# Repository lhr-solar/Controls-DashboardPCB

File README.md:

# Controls Leader

This board is the central hub for human machine interface inputs on the vehicle. It reads switch states, detects faults, and coordinates lighting commands across the vehicle network while maintaining robust error reporting.

## Hardware Architecture

### Power Delivery

- Main 24 V supply with ground input
- Buck regulator for MCU and Peripheral Sensing/Output Modules (PSOMs)
- Isolated power and ground dedicated to CAN interface(s)

### CAN Interfaces

- **2× CAN Transceiver Chips** with dedicated in/out connector pairs:
  - Controls CAN (lighting/peripheral network)
  - Car CAN (vehicle state network)

### Input Interfaces

#### Dashboard I/O

- Ignition switch
- Gear selector switch
- Cruise control enable/set buttons
- Regen enable button
- Hazard lights switch
- Supplemental battery switch (isolated input)

#### Steering Wheel I/O

- Left/right turn indicators
- Horn button
- Regen active indicator

## Software Functionality
TBD

## Repository Structure

```
hardware/
├── ControlsLeader_PCB/
│   ├── jkcpcb/
│   ├── lib/
│   ├── *.kicad_sch (schematic files)
│   └── *.kicad_pcb (PCB layout)
├── 3d_models/
├── Silkscreens/
└── fab/

firmware/

```

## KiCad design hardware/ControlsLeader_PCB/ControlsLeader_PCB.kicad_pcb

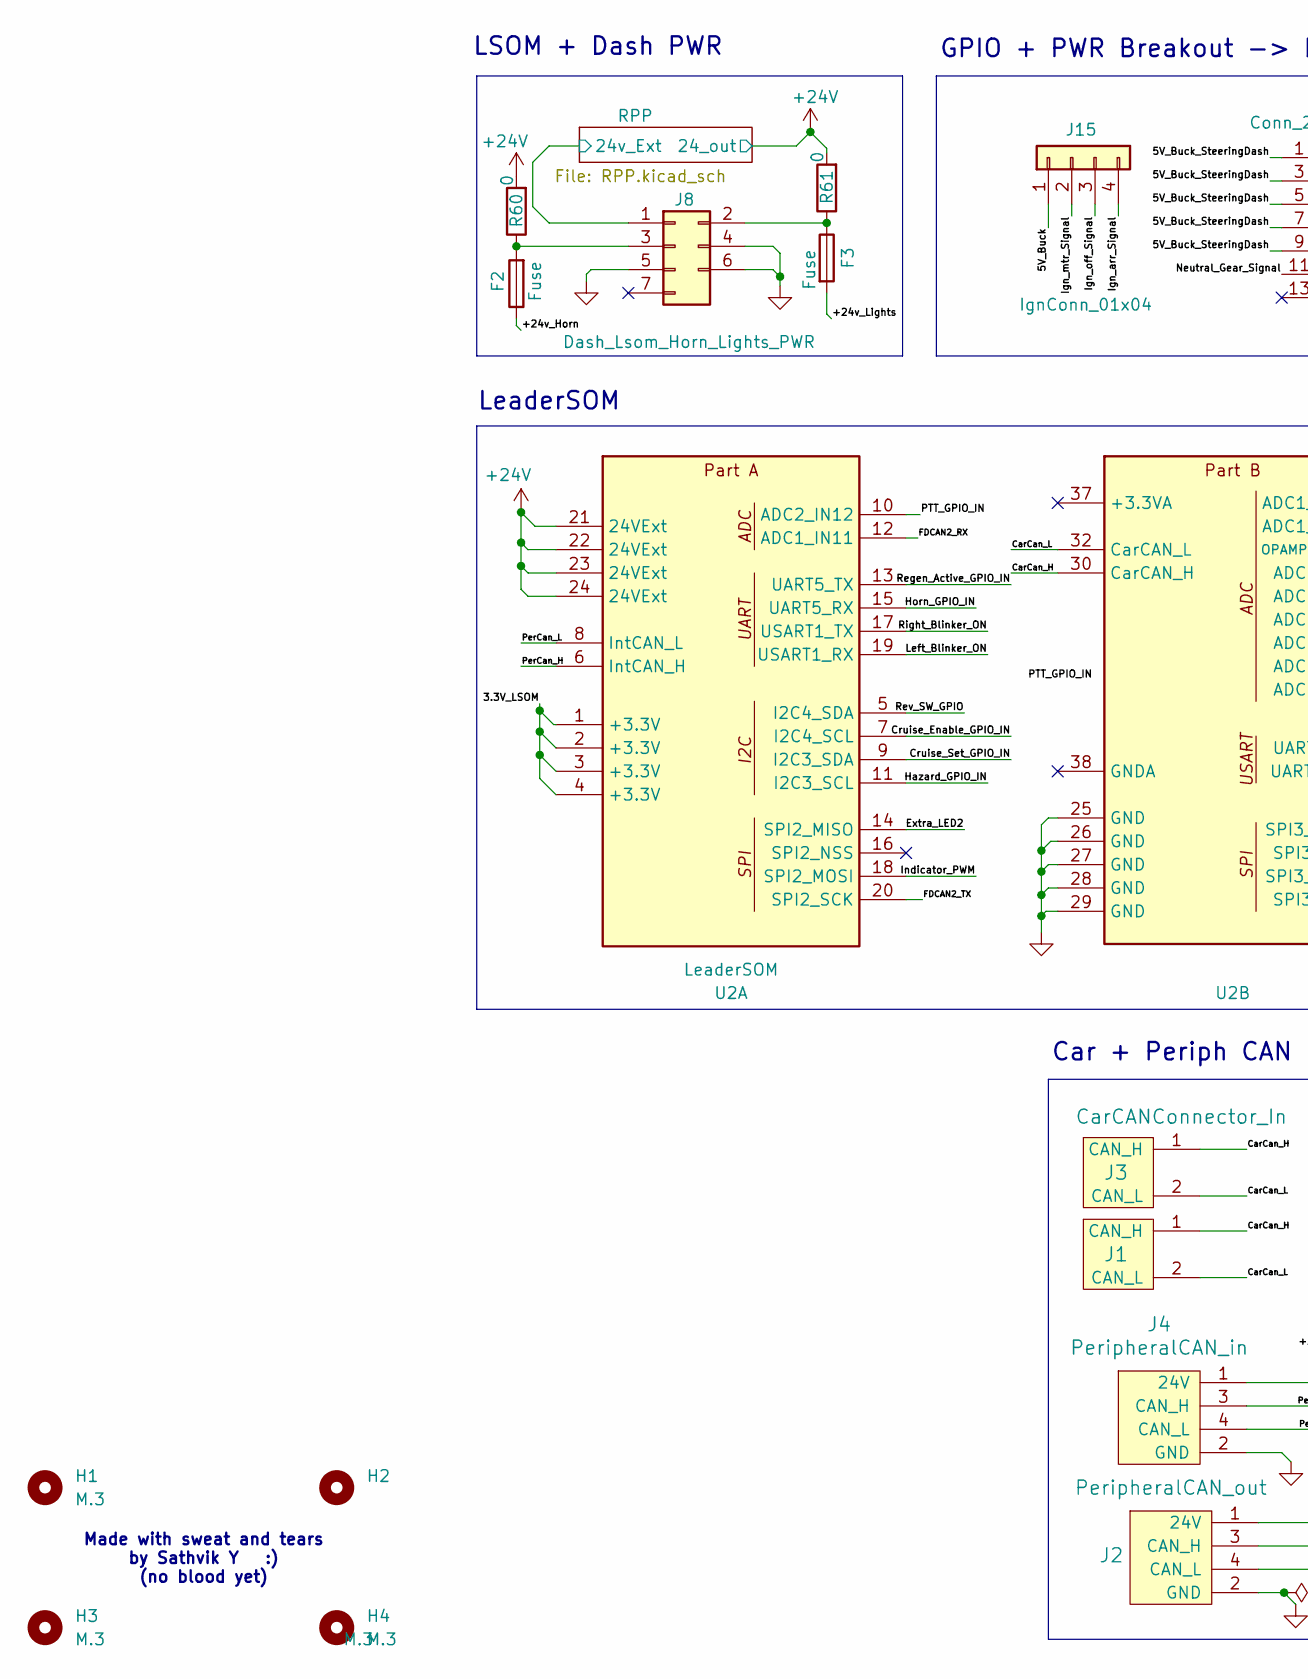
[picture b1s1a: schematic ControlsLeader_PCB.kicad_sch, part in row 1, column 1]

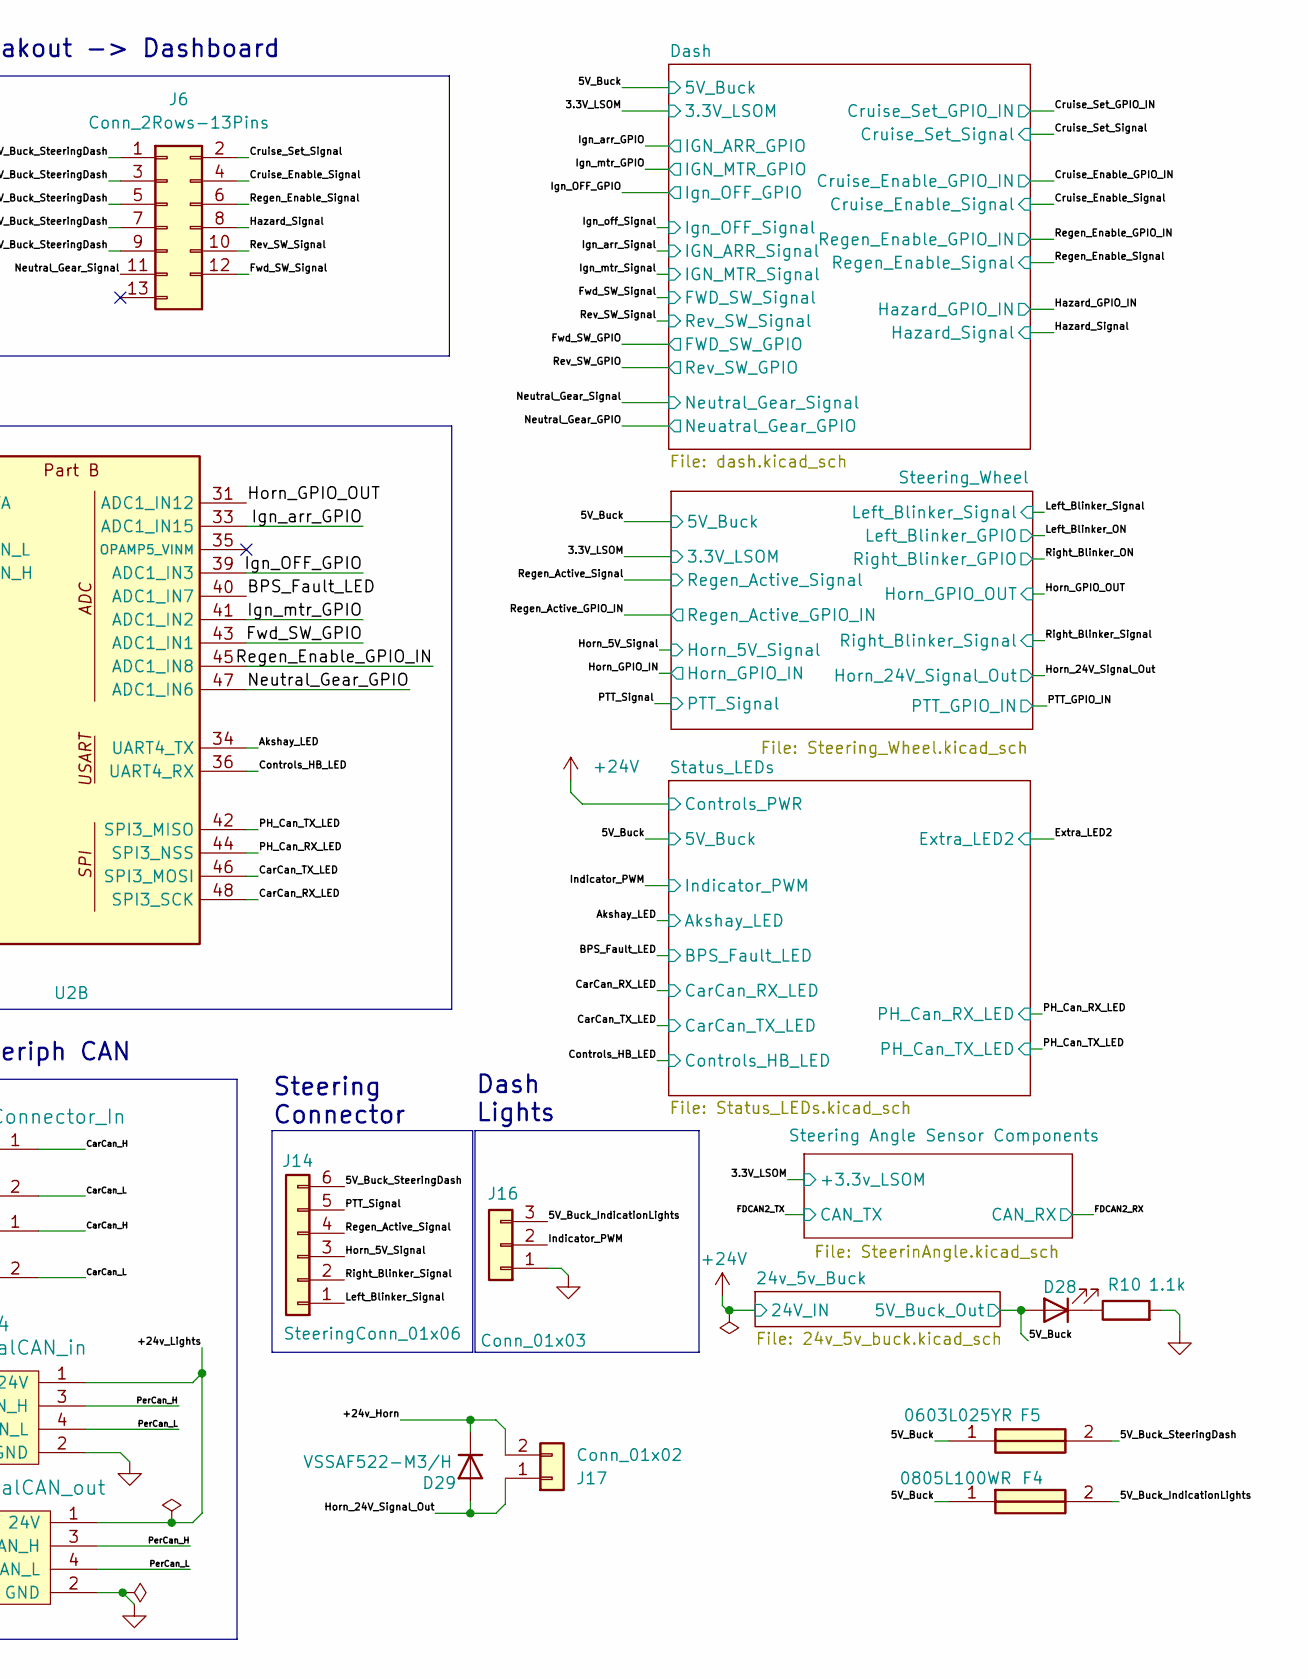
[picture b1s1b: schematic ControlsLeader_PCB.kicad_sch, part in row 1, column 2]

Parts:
D28: Controls_Leader_Status_Red; LED_0603_1608Metric_Pad1.05x0.95mm_HandSolder
D29: VSSAF522-M3/H; D_SOD-123F
F2, F3: Fuse; Fuseholder_Blade_Mini_Keystone_3568
F4: 0805L100WR; FUSC2114X180N; Mouser Part Number 576-0805L100
F5: 0603L025YR; FUSC1608X75N; Mouser Part Number 576-0603L025YR
H1, H2, H3, H4: M.3; MountingHole_3.2mm_M3_Pad_TopBottom
J1: CarCANConnector_Out; Molex_Nano-Fit_105313-xx02_1x02_P2.50mm_Horizontal
J2: PeripheralCAN_out; Molex_Nano-Fit_105313-xx04_1x04_P2.50mm_Horizontal
J3: CarCANConnector_In; Molex_Nano-Fit_105313-xx02_1x02_P2.50mm_Horizontal
J4: PeripheralCAN_in; Molex_Nano-Fit_105313-xx04_1x04_P2.50mm_Horizontal
J6: Conn_2Rows-13Pins; Molex_Nano-Fit_105314-xx12_2x06_P2.50mm_Horizontal
J8: Dash_Lsom_Horn_Lights_PWR; Molex_Nano-Fit_105314-xx06_2x03_P2.50mm_Horizontal
J14: SteeringConn_01x06; Molex_Nano-Fit_105313-xx06_1x06_P2.50mm_Horizontal
J15: IgnConn_01x04; Molex_Nano-Fit_105313-xx04_1x04_P2.50mm_Horizontal
J16: Conn_01x03; Molex_Nano-Fit_105313-xx03_1x03_P2.50mm_Horizontal
J17: Conn_01x02; Molex_Nano-Fit_105313-xx02_1x02_P2.50mm_Horizontal
R10: 1.1k; R_0603_1608Metric_Pad0.98x0.95mm_HandSolder
R60, R61: 0; R_0603_1608Metric_Pad0.98x0.95mm_HandSolder
U2: LeaderSOM

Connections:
+24V: R60.2, R61.2, U2.21 (24VExt), U2.22 (24VExt), U2.23 (24VExt), U2.24 (24VExt); also elsewhere on the board
/3.3V_LSOM: U2.1 (+3.3V), U2.2 (+3.3V), U2.3 (+3.3V), U2.4 (+3.3V); also elsewhere on the board
/5V_Buck: D28.2 (A), F4.1, F5.1, J15.1; also elsewhere on the board
/5V_Buck_IndicationLights: F4.2, J16.3
/5V_Buck_SteeringDash: F5.2, J6.1, J6.3, J6.5, J6.7, J6.9, J14.6
/+24v_Horn: D29.1 (K), F2.1, J17.2
/+24v_Lights: F3.2, J2.1 (24V), J4.1 (24V)
/Akshay_LED: U2.34 (UART4_TX); also elsewhere on the board
/BPS_Fault_LED: U2.40 (ADC1_IN7); also elsewhere on the board
/CarCan_H: J1.1 (CAN_H), J3.1 (CAN_H), U2.30 (CarCAN_H)
/CarCan_L: J1.2 (CAN_L), J3.2 (CAN_L), U2.32 (CarCAN_L)
/CarCan_RX_LED: U2.48 (SPI3_SCK); also elsewhere on the board
/CarCan_TX_LED: U2.46 (SPI3_MOSI); also elsewhere on the board
/Controls_HB_LED: U2.36 (UART4_RX); also elsewhere on the board
/Cruise_Enable_GPIO_IN: U2.7 (I2C4_SCL); also elsewhere on the board
/Cruise_Enable_Signal: J6.4; also elsewhere on the board
/Cruise_Set_GPIO_IN: U2.9 (I2C3_SDA); also elsewhere on the board
/Cruise_Set_Signal: J6.2; also elsewhere on the board
/Extra_LED2: U2.14 (SPI2_MISO); also elsewhere on the board
/FDCAN2_RX: U2.12 (ADC1_IN11); also elsewhere on the board
/FDCAN2_TX: U2.20 (SPI2_SCK); also elsewhere on the board
/Fwd_SW_GPIO: U2.43 (ADC1_IN1); also elsewhere on the board
/Fwd_SW_Signal: J6.12; also elsewhere on the board
/Hazard_GPIO_IN: U2.11 (I2C3_SCL); also elsewhere on the board
/Hazard_Signal: J6.8; also elsewhere on the board
/Horn_5V_Signal: J14.3; also elsewhere on the board
/Horn_24V_Signal_Out: D29.2 (A), J17.1; also elsewhere on the board
/Horn_GPIO_IN: U2.15 (UART5_RX); also elsewhere on the board
/Horn_GPIO_OUT: U2.31 (ADC1_IN12); also elsewhere on the board
/Ign_OFF_GPIO: U2.39 (ADC1_IN3); also elsewhere on the board
/Ign_arr_GPIO: U2.33 (ADC1_IN15); also elsewhere on the board
/Ign_arr_Signal: J15.4; also elsewhere on the board
/Ign_mtr_GPIO: U2.41 (ADC1_IN2); also elsewhere on the board
/Ign_mtr_Signal: J15.2; also elsewhere on the board
/Ign_off_Signal: J15.3; also elsewhere on the board
/Indicator_PWM: J16.2, U2.18 (SPI2_MOSI)
/Left_Blinker_ON: U2.19 (USART1_RX); also elsewhere on the board
/Left_Blinker_Signal: J14.1; also elsewhere on the board
/Neutral_Gear_GPIO: U2.47 (ADC1_IN6); also elsewhere on the board
/Neutral_Gear_Signal: J6.11; also elsewhere on the board
/PH_Can_RX_LED: U2.44 (SPI3_NSS); also elsewhere on the board
/PH_Can_TX_LED: U2.42 (SPI3_MISO); also elsewhere on the board
/PTT_GPIO_IN: U2.10 (ADC2_IN12); also elsewhere on the board
/PTT_Signal: J14.5; also elsewhere on the board
/PerCan_H: J2.3 (CAN_H), J4.3 (CAN_H), U2.6 (IntCAN_H)
/PerCan_L: J2.4 (CAN_L), J4.4 (CAN_L), U2.8 (IntCAN_L)
/RPP/LV+: J8.1; also elsewhere on the board
/Regen_Active_GPIO_IN: U2.13 (UART5_TX); also elsewhere on the board
/Regen_Active_Signal: J14.4; also elsewhere on the board
/Regen_Enable_GPIO_IN: U2.45 (ADC1_IN8); also elsewhere on the board
/Regen_Enable_Signal: J6.6; also elsewhere on the board
/Rev_SW_GPIO: U2.5 (I2C4_SDA); also elsewhere on the board
/Rev_SW_Signal: J6.10; also elsewhere on the board
/Right_Blinker_ON: U2.17 (USART1_TX); also elsewhere on the board
/Right_Blinker_Signal: J14.2; also elsewhere on the board
GND: J2.2 (GND), J4.2 (GND), J8.4, J8.5, J8.6, J16.1, R10.2, U2.25 (GND), U2.26 (GND), U2.27 (GND), U2.28 (GND), U2.29 (GND); also elsewhere on the board
unnamed: D28.1 (K), R10.1
unnamed: F3.1, J8.2, R61.1
unnamed: F2.2, J8.3, R60.1

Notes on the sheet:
Car + Periph CAN
Dash Lights
GPIO + PWR Breakout -> Dashboard
Steering Connector
LSOM + Dash PWR
LeaderSOM
Made with sweat and tears by Sathvik Y :) (no blood yet)

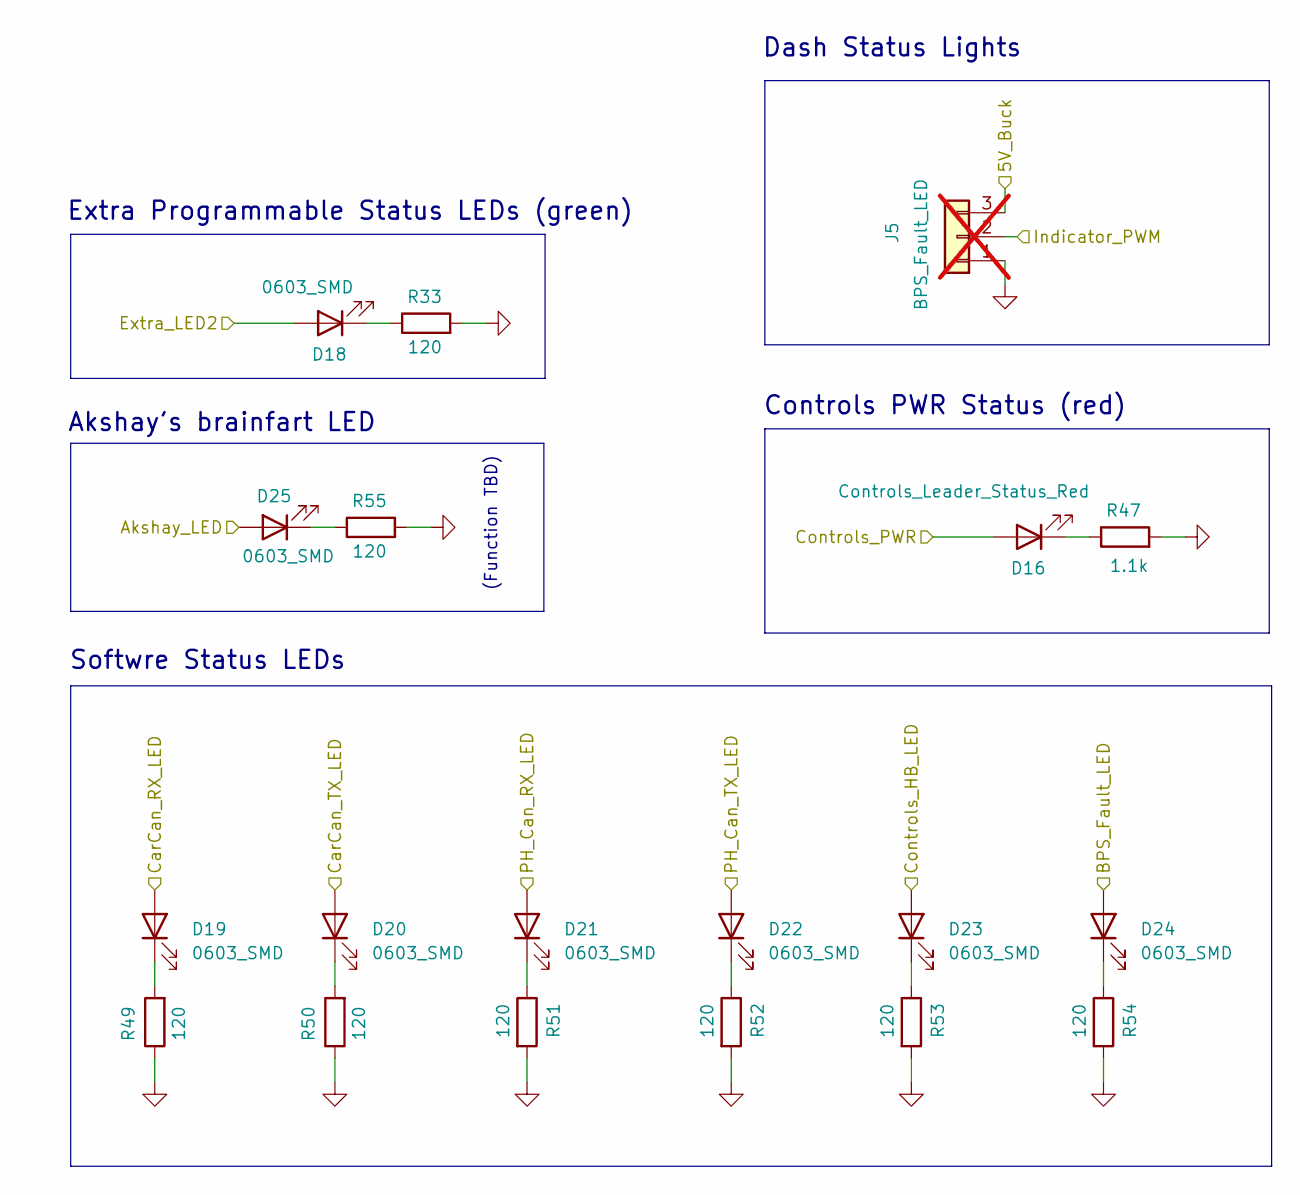
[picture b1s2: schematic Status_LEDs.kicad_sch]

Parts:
D16: Controls_Leader_Status_Red; LED_0603_1608Metric_Pad1.05x0.95mm_HandSolder
D18, D19, D20, D21, D22, D23, D24, D25: 0603_SMD; LED_0603_1608Metric_Pad1.05x0.95mm_HandSolder
J5: BPS_Fault_LED; Molex_Micro-Fit_3.0_43650-0300_1x03_P3.00mm_Horizontal; not fitted
R33, R49, R50, R51, R52, R53, R54, R55: 120; R_0603_1608Metric_Pad0.98x0.95mm_HandSolder
R47: 1.1k; R_0603_1608Metric_Pad0.98x0.95mm_HandSolder

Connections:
+24V: D16.2 (A); also elsewhere on the board
/Akshay_LED: D25.2 (A); also elsewhere on the board
/BPS_Fault_LED: D24.2 (A); also elsewhere on the board
/CarCan_RX_LED: D19.2 (A); also elsewhere on the board
/CarCan_TX_LED: D20.2 (A); also elsewhere on the board
/Controls_HB_LED: D23.2 (A); also elsewhere on the board
/Extra_LED2: D18.2 (A); also elsewhere on the board
/PH_Can_RX_LED: D21.2 (A); also elsewhere on the board
/PH_Can_TX_LED: D22.2 (A); also elsewhere on the board
GND: J5.1, R33.2, R47.2, R49.1, R50.1, R51.2, R52.2, R53.2, R54.2, R55.2; also elsewhere on the board
unnamed: D16.1 (K), R47.1
unnamed: D18.1 (K), R33.1
unnamed: D19.1 (K), R49.2
unnamed: D20.1 (K), R50.2
unnamed: D21.1 (K), R51.1
unnamed: D22.1 (K), R52.1
unnamed: D23.1 (K), R53.1
unnamed: D24.1 (K), R54.1
unnamed: D25.1 (K), R55.1

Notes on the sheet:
Akshay's brainfart LED
Extra Programmable Status LEDs (green)
Softwre Status LEDs
Controls PWR Status (red)
(Function TBD)
Dash Status Lights

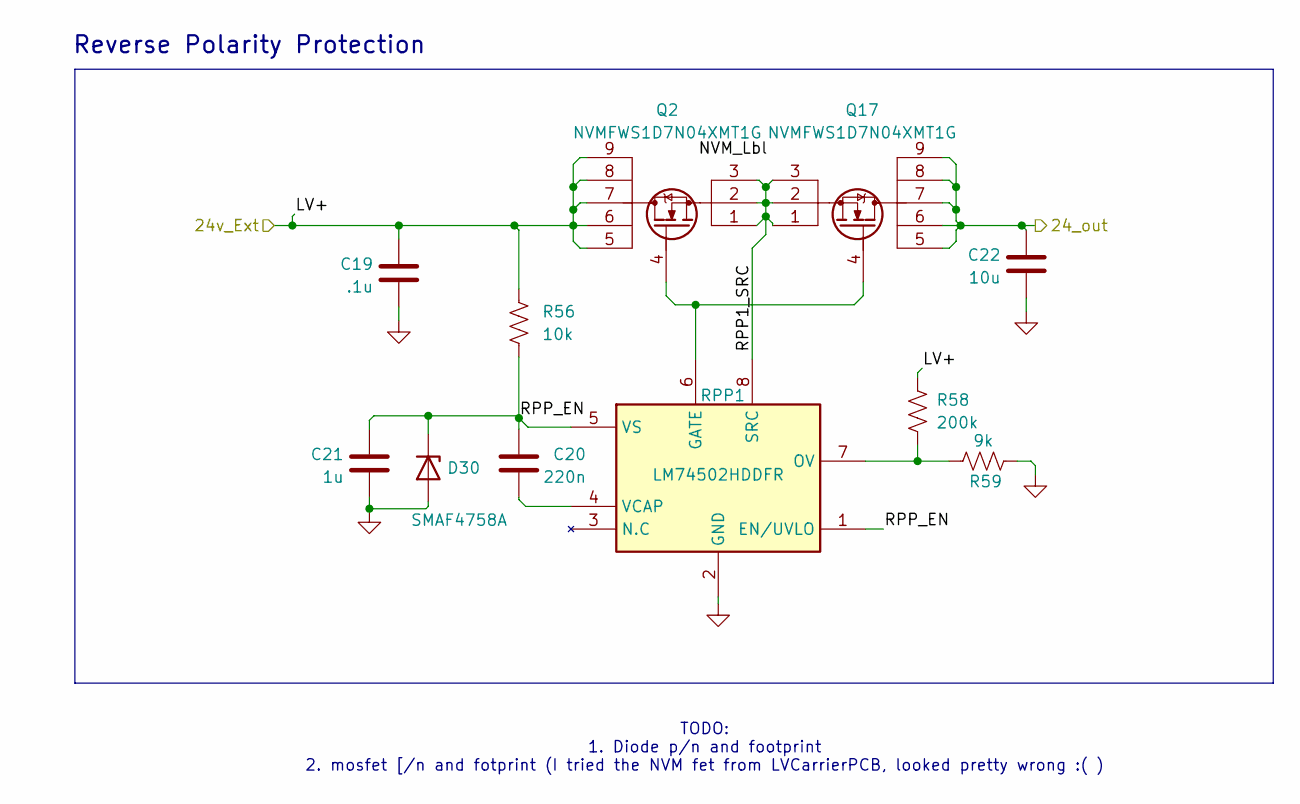
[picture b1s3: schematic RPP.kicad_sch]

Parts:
C19: .1u; C_0603_1608Metric_Pad1.08x0.95mm_HandSolder; Manufacturer_Part_Number 06035C223K4T4A
C20: 220n; C_0603_1608Metric_Pad1.08x0.95mm_HandSolder; Manufacturer_Part_Number 06035C223K4T4A
C21: 1u; C_0603_1608Metric_Pad1.08x0.95mm_HandSolder; Manufacturer_Part_Number 06035C223K4T4A
C22: 10u; C_0603_1608Metric_Pad1.08x0.95mm_HandSolder; Manufacturer_Part_Number 06035C223K4T4A
D30: SMAF4758A; SODFL5026X125N
Q2, Q17: NVMFWS1D7N04XMT1G; NVMFWS3D0P04M8LT1G
R56: 10k; R_0603_1608Metric_Pad0.98x0.95mm_HandSolder; Manufacturer_Part_Number CRCW060310K0FKEI
R58: 200k; R_0603_1608Metric_Pad0.98x0.95mm_HandSolder; Manufacturer_Part_Number CRCW060310K0FKEI
R59: 9k; R_0603_1608Metric_Pad0.98x0.95mm_HandSolder; Manufacturer_Part_Number CRCW060310K0FKEI
RPP1: LM74502HDDFR; SOT65P280X110-8N; Mouser Part Number 595-LM74502HDDFR

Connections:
+24V: C22.2, Q17.5, Q17.6, Q17.7, Q17.8, Q17.9; also elsewhere on the board
/RPP/LV+: C19.2, Q2.5, Q2.6, Q2.7, Q2.8, Q2.9, R56.1, R58.1; also elsewhere on the board
/RPP/RPP1_SRC: Q2.1, Q2.2, Q2.3, Q17.1, Q17.2, Q17.3, RPP1.8 (SRC)
/RPP/RPP_EN: C20.2, C21.2, D30.1 (K), R56.2, RPP1.1 (EN/UVLO), RPP1.5 (VS)
GND: C19.1, C21.1, C22.1, D30.2 (A), R59.2, RPP1.2 (GND); also elsewhere on the board
unnamed: Q2.4, Q17.4, RPP1.6 (GATE)
unnamed: R58.2, R59.1, RPP1.7 (OV)
unnamed: C20.1, RPP1.4 (VCAP)

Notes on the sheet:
TODO: 1. Diode p/n and footprint 2. mosfet [/n and fotprint (I tried the NVM fet from LVCarrierPCB, looked pretty wrong :( )
Reverse Polarity Protection

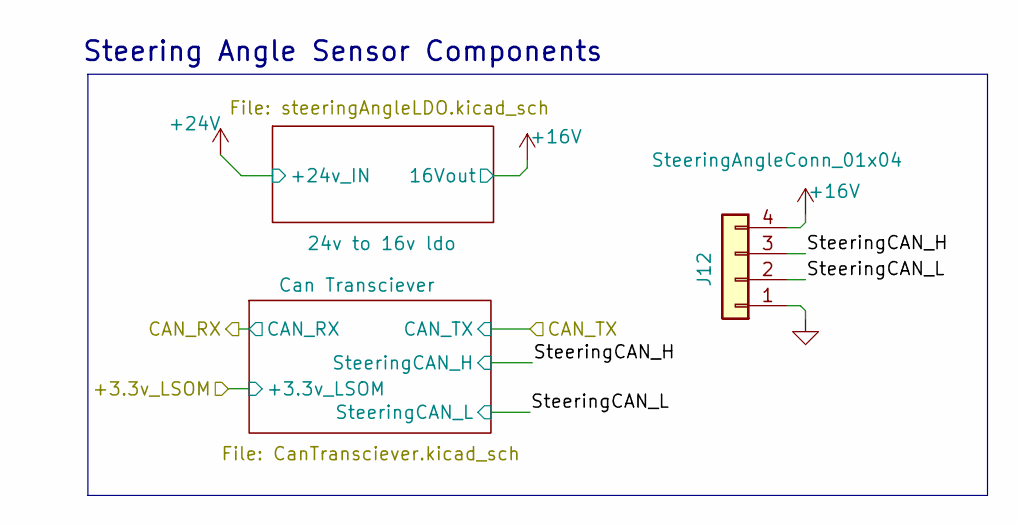
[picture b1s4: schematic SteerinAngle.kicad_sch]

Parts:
J12: SteeringAngleConn_01x04; Molex_Nano-Fit_105313-xx04_1x04_P2.50mm_Horizontal

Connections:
+16V: J12.4; also elsewhere on the board
/Steering Angle Sensor Components/SteeringCAN_H: J12.3; also elsewhere on the board
/Steering Angle Sensor Components/SteeringCAN_L: J12.2; also elsewhere on the board
GND: J12.1; also elsewhere on the board

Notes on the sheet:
Steering Angle Sensor Components

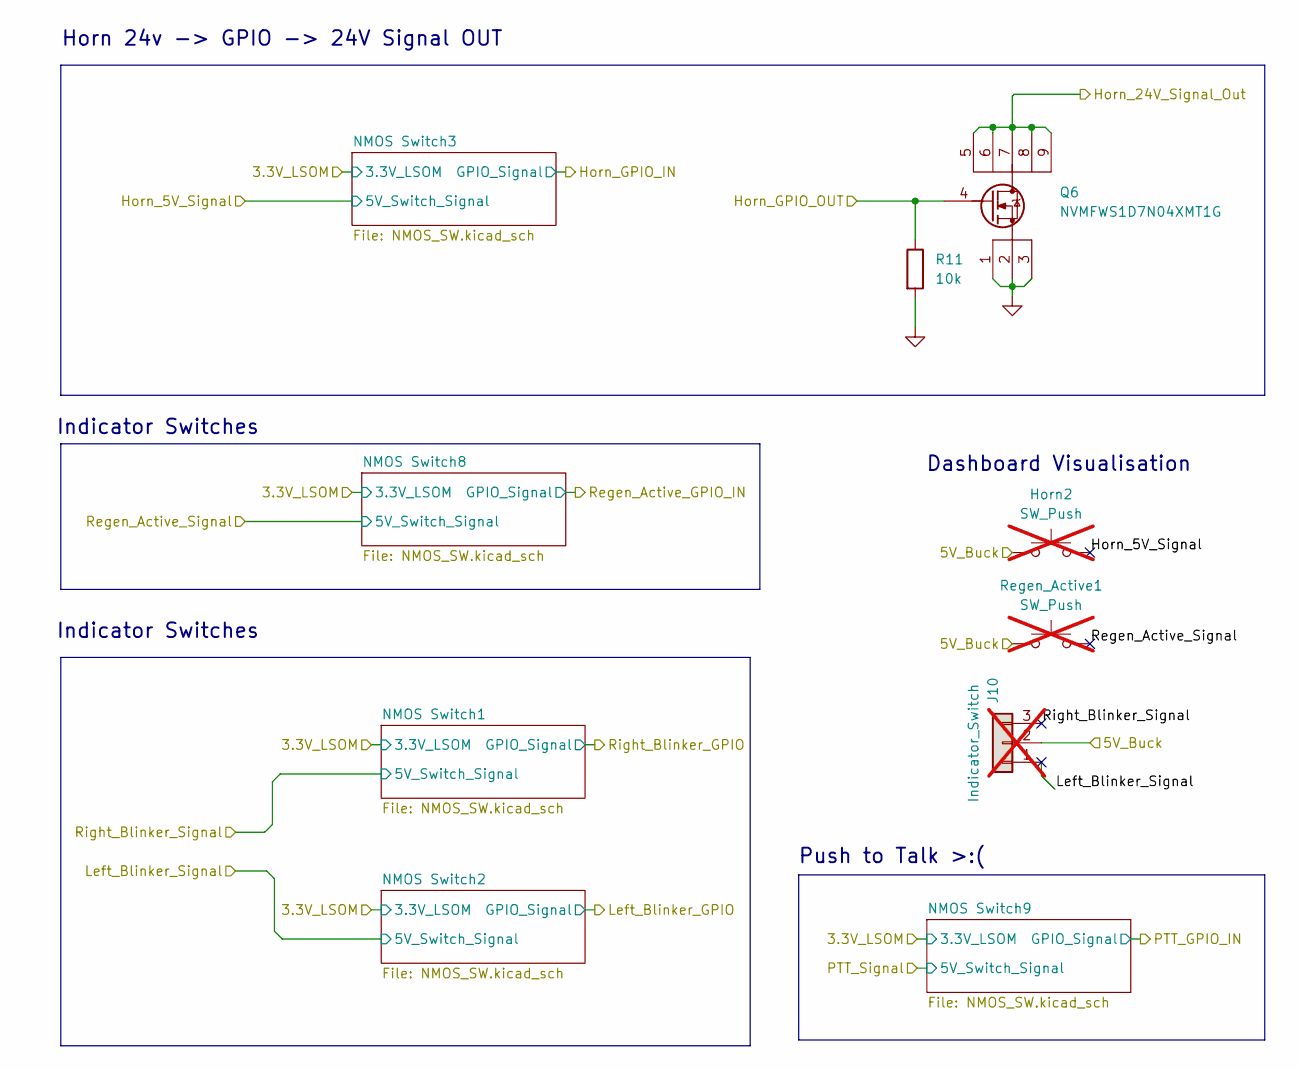
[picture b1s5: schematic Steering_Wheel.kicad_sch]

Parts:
Horn2: SW_Push; Molex_Nano-Fit_105313-xx02_1x02_P2.50mm_Horizontal; not fitted
J10: Indicator_Switch; Molex_Nano-Fit_105313-xx03_1x03_P2.50mm_Horizontal; not fitted
Q6: NVMFWS1D7N04XMT1G; NVMFWS3D0P04M8LT1G
R11: 10k; R_0603_1608Metric_Pad0.98x0.95mm_HandSolder
Regen_Active1: SW_Push; Molex_Nano-Fit_105313-xx02_1x02_P2.50mm_Horizontal; not fitted

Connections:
/Horn_24V_Signal_Out: Q6.5, Q6.6, Q6.7, Q6.8, Q6.9; also elsewhere on the board
/Horn_GPIO_OUT: Q6.4, R11.1; also elsewhere on the board
GND: Q6.1, Q6.2, Q6.3, R11.2; also elsewhere on the board
unnamed: Horn2.1, J10.2, Regen_Active1.1

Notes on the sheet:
Push to Talk >:(
Indicator Switches
Horn 24v -> GPIO -> 24V Signal OUT
Dashboard Visualisation

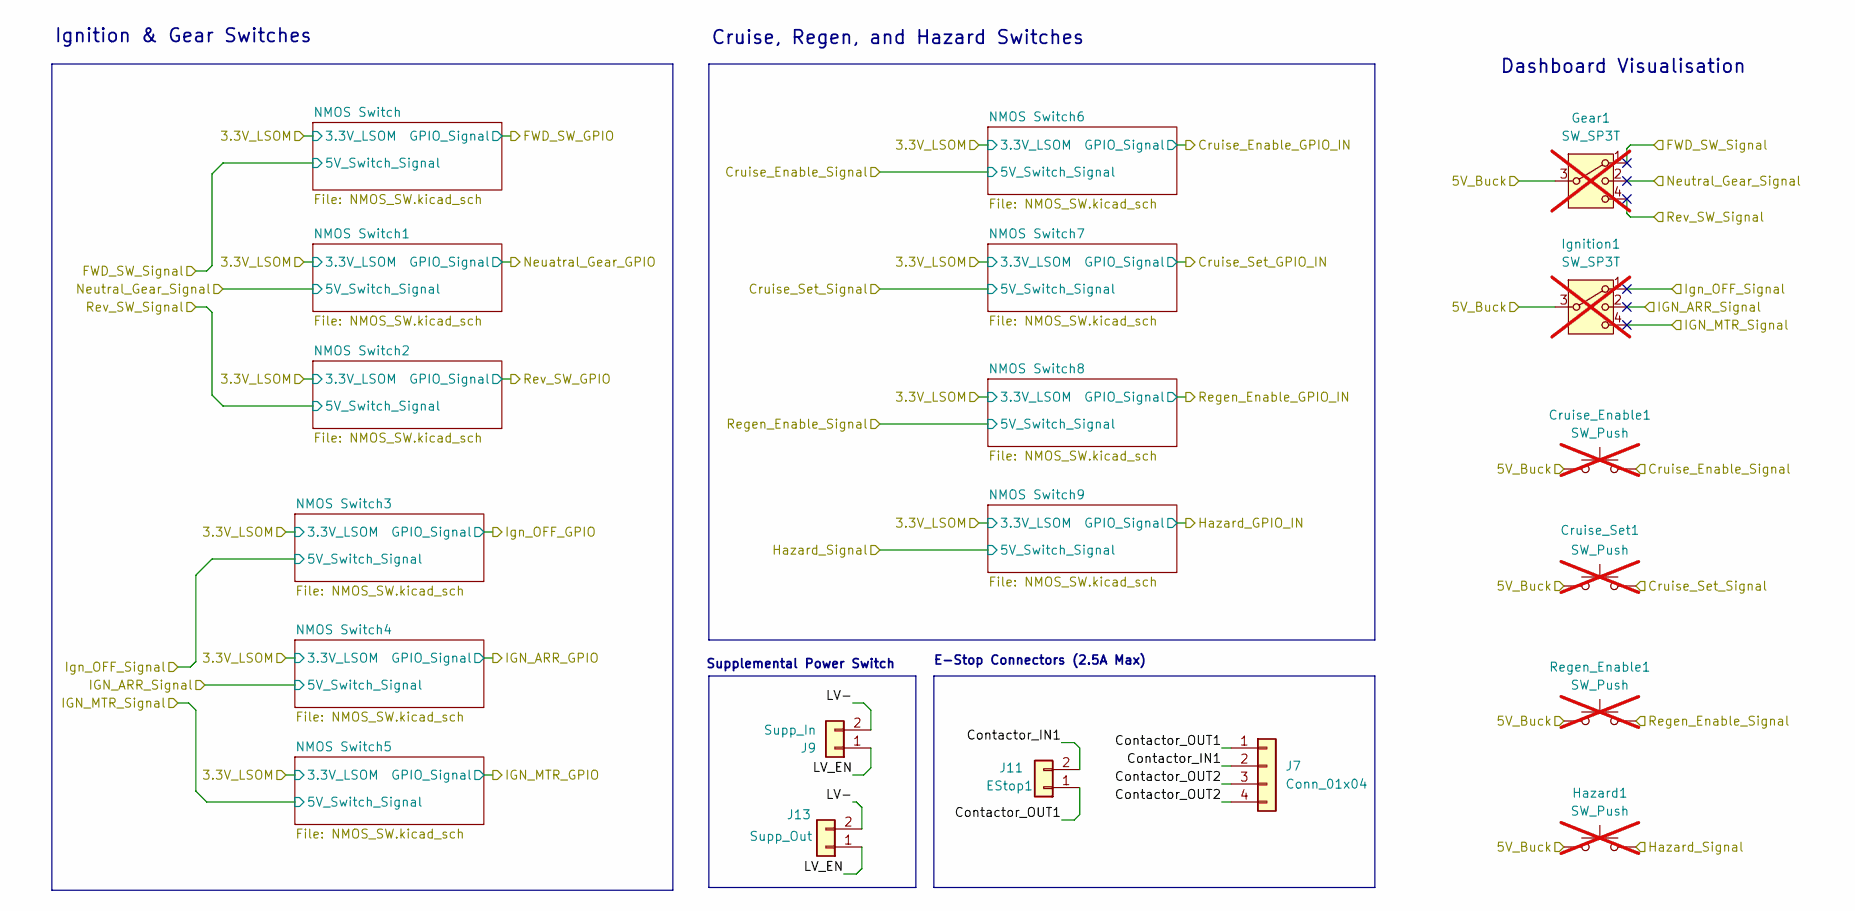
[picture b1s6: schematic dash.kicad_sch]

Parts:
Cruise_Enable1: SW_Push; Molex_Nano-Fit_105313-xx02_1x02_P2.50mm_Horizontal; not fitted
Cruise_Set1: SW_Push; Molex_Nano-Fit_105313-xx02_1x02_P2.50mm_Horizontal; not fitted
Gear1: SW_SP3T; CONN_SD-105313-100_04_MOL; not fitted
Hazard1: SW_Push; Molex_Nano-Fit_105313-xx02_1x02_P2.50mm_Horizontal; not fitted
Ignition1: SW_SP3T; CONN_SD-105313-100_04_MOL; not fitted
J7: Conn_01x04; Molex_Nano-Fit_105313-xx04_1x04_P2.50mm_Horizontal
J9: Supp_In; Molex_Nano-Fit_105313-xx02_1x02_P2.50mm_Horizontal
J11: EStop1; Molex_Nano-Fit_105313-xx02_1x02_P2.50mm_Horizontal
J13: Supp_Out; Molex_Nano-Fit_105313-xx02_1x02_P2.50mm_Horizontal
Regen_Enable1: SW_Push; Molex_Nano-Fit_105313-xx02_1x02_P2.50mm_Horizontal; not fitted

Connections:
/Dash/Contactor_IN1: J7.2, J11.2
/Dash/Contactor_OUT1: J7.1, J11.1
/Dash/Contactor_OUT2: J7.3, J7.4
/Dash/LV-: J9.2, J13.2
/Dash/LV_EN: J9.1, J13.1
unnamed: Cruise_Enable1.1, Cruise_Set1.1, Gear1.3, Hazard1.1, Ignition1.3, Regen_Enable1.1

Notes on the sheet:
E-Stop Connectors (2.5A Max)
Dashboard Visualisation
Cruise, Regen, and Hazard Switches
Ignition & Gear Switches
Supplemental Power Switch

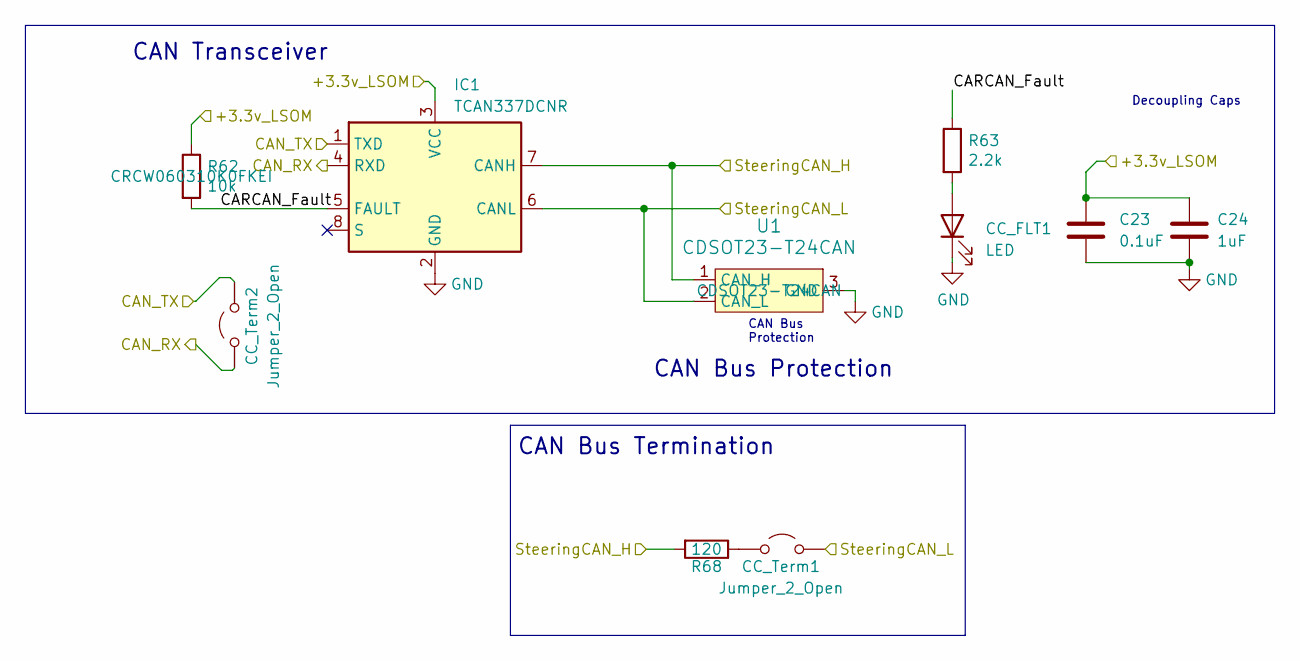
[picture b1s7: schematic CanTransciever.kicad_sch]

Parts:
C23: 0.1uF; C_0603_1608Metric_Pad1.08x0.95mm_HandSolder; Mouser Part Number MLASH168SB7104KTNA01
C24: 1uF; C_0603_1608Metric_Pad1.08x0.95mm_HandSolder; Mouser Part Number MLASU168SB5105KTNA01
CC_FLT1: LED; LED_0603_1608Metric_Pad1.05x0.95mm_HandSolder; Mouser Part Number 604-APTD2012LCGCK
CC_Term1, CC_Term2: Jumper_2_Open; PinHeader_1x02_P2.54mm_Vertical
IC1: TCAN337DCNR; Mouser Part Number 595-TCAN337DCNR
R62: 10k; R_0603_1608Metric_Pad0.98x0.95mm_HandSolder; Mouser Part Number CRCW060310K0FKEI
R63: 2.2k; R_0603_1608Metric_Pad0.98x0.95mm_HandSolder; Mouser Part Number CRCW06032K10FKEA
R68: 120; R_0603_1608Metric_Pad0.98x0.95mm_HandSolder; Mouser Part Number CRCW0603120RFKEC
U1: CDSOT23-T24CAN; Mouser Part Number CDSOT23-T24CAN

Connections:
/3.3V_LSOM: C23.1, C24.1, IC1.3 (VCC), R62.1; also elsewhere on the board
/FDCAN2_RX: CC_Term2.1 (A), IC1.4 (RXD); also elsewhere on the board
/FDCAN2_TX: CC_Term2.2 (B), IC1.1 (TXD); also elsewhere on the board
/Steering Angle Sensor Components/Can Transciever/CARCAN_Fault: IC1.5 (FAULT), R62.2, R63.1
/Steering Angle Sensor Components/SteeringCAN_H: IC1.7 (CANH), R68.2, U1.1 (CAN_H); also elsewhere on the board
/Steering Angle Sensor Components/SteeringCAN_L: CC_Term1.2 (B), IC1.6 (CANL), U1.2 (CAN_L); also elsewhere on the board
GND: C23.2, C24.2, CC_FLT1.1 (K), IC1.2 (GND), U1.3 (GND); also elsewhere on the board
unnamed: CC_FLT1.2 (A), R63.2
unnamed: CC_Term1.1 (A), R68.1

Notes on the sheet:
CAN Bus Protection
Decoupling Caps
CAN Bus Protection
CAN Transceiver
CAN Bus Termination

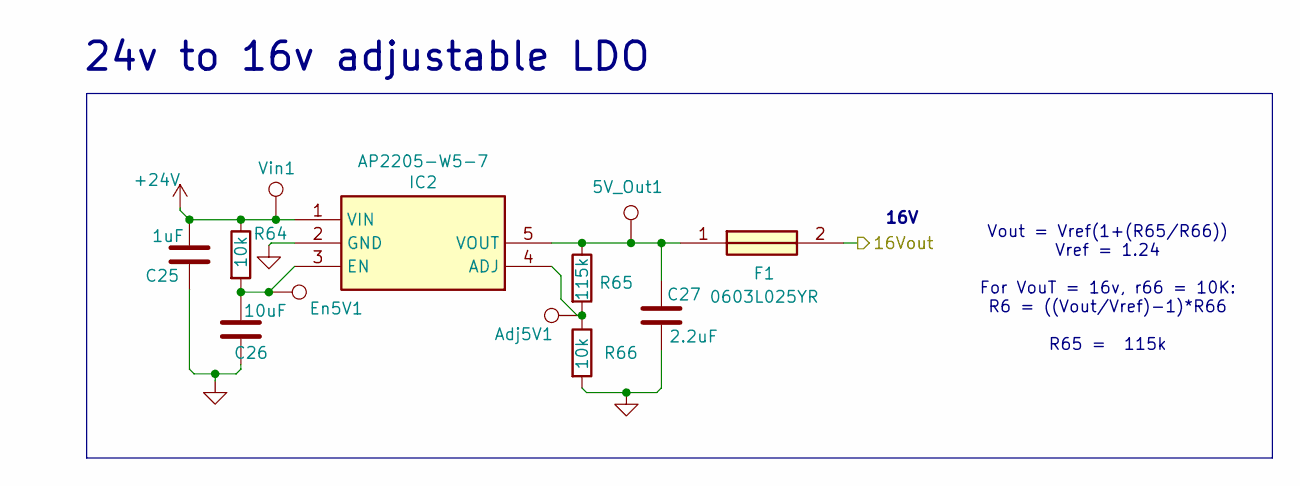
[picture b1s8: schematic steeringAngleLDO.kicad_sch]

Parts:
5V_Out1: 5V_Out; TestPoint_Pad_1.0x1.0mm
Adj5V1: Adj5V; TestPoint_Pad_1.0x1.0mm
C25: 1uF; C_0603_1608Metric_Pad1.08x0.95mm_HandSolder
C26: 10uF; C_0603_1608Metric_Pad1.08x0.95mm_HandSolder
C27: 2.2uF; C_0603_1608Metric_Pad1.08x0.95mm_HandSolder
En5V1: Enable5V; TestPoint_Pad_1.0x1.0mm
F1: 0603L025YR; FUSC1608X75N; Mouser Part Number 576-0603L025YR
IC2: AP2205-W5-7; AP2205W57; Mouser Part Number 621-AP2205-W5-7
R64, R66: 10k; R_0603_1608Metric_Pad0.98x0.95mm_HandSolder
R65: 115k; R_0603_1608Metric_Pad0.98x0.95mm_HandSolder
Vin1: Vin; TestPoint_Pad_1.0x1.0mm

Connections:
+16V: F1.2; also elsewhere on the board
+24V: C25.2, IC2.1 (VIN), R64.1, Vin1.1; also elsewhere on the board
/Steering Angle Sensor Components/24v to 16v ldo/16v_prefuse: 5V_Out1.1, C27.1, F1.1, IC2.5 (VOUT), R65.1; also elsewhere on the board
GND: C25.1, C26.1, C27.2, IC2.2 (GND), R66.2; also elsewhere on the board
unnamed 100: Adj5V1.1, IC2.4 (ADJ), R65.2, R66.1; also elsewhere on the board
unnamed 101: C26.2, En5V1.1, IC2.3 (EN), R64.2; also elsewhere on the board

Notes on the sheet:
Vout = Vref(1+(R65/R66)) Vref = 1.24 For VouT = 16v, r66 = 10K: R6 = ((Vout/Vref)-1)*R66 R65 = 115k
24v to 16v adjustable LDO
16V

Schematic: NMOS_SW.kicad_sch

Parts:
C1: 2.2uF; C_0603_1608Metric_Pad1.08x0.95mm_HandSolder
D1: GPIO_Status_Blue; LED_0603_1608Metric_Pad1.05x0.95mm_HandSolder
Q1: NMOS; SOT23
R1: 10k; R_0603_1608Metric_Pad0.98x0.95mm_HandSolder
R9: 150; R_0603_1608Metric_Pad0.98x0.95mm_HandSolder
R31: 100k; R_0603_1608Metric_Pad0.98x0.95mm_HandSolder
TP1: TestPoint; TestPoint_Pad_1.0x1.0mm

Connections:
/3.3V_LSOM: R31.1; also elsewhere on the board
/Regen_Active_GPIO_IN: Q1.1 (D), R31.2, TP1.1; also elsewhere on the board
/Regen_Active_Signal: C1.2, D1.2 (A), Q1.2 (G), R1.2; also elsewhere on the board
GND: C1.1, Q1.3 (S), R1.1, R9.2; also elsewhere on the board
unnamed: D1.1 (K), R9.1

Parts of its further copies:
C2, C3, C4, C5, C6, C7, C8, C9, C10, C11, C12, C13, C14, C28: 2.2uF; C_0603_1608Metric_Pad1.08x0.95mm_HandSolder
D2, D3, D5, D6, D7, D8, D9, D10, D11, D12, D13, D14, D15, D17: GPIO_Status_Blue; LED_0603_1608Metric_Pad1.05x0.95mm_HandSolder
Q3, Q4, Q5, Q7, Q8, Q9, Q10, Q11, Q12, Q13, Q14, Q15, Q16, Q18: NMOS; SOT23
R2, R3, R4, R5, R6, R7, R8, R12, R13, R14, R15, R16, R17, R45: 10k; R_0603_1608Metric_Pad0.98x0.95mm_HandSolder
R18, R19, R20, R21, R22, R23, R24, R25, R26, R27, R28, R29, R30, R46: 150; R_0603_1608Metric_Pad0.98x0.95mm_HandSolder
R32, R34, R35, R36, R37, R38, R39, R40, R41, R42, R43, R44, R57, R67: 100k; R_0603_1608Metric_Pad0.98x0.95mm_HandSolder
TP2, TP3, TP4, TP5, TP6, TP7, TP8, TP9, TP10, TP11, TP12, TP13, TP14, TP15: TestPoint; TestPoint_Pad_1.0x1.0mm

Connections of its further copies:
/3.3V_LSOM: R32.1, R34.1, R35.1, R36.1, R37.1, R38.1, R39.1, R40.1, R41.1, R42.1, R43.1, R44.1, R57.1, R67.1; also elsewhere on the board
/Cruise_Enable_GPIO_IN: Q10.1 (D), R39.2, TP8.1; also elsewhere on the board
/Cruise_Enable_Signal: C8.2, D9.2 (A), Q10.2 (G), R8.2; also elsewhere on the board
/Cruise_Set_GPIO_IN: Q11.1 (D), R40.2, TP9.1; also elsewhere on the board
/Cruise_Set_Signal: C9.2, D10.2 (A), Q11.2 (G), R12.2; also elsewhere on the board
/Fwd_SW_GPIO: Q3.1 (D), R32.2, TP2.1; also elsewhere on the board
/Fwd_SW_Signal: C2.2, D2.2 (A), Q3.2 (G), R2.2; also elsewhere on the board
/Hazard_GPIO_IN: Q13.1 (D), R42.2, TP11.1; also elsewhere on the board
/Hazard_Signal: C11.2, D12.2 (A), Q13.2 (G), R14.2; also elsewhere on the board
/Horn_5V_Signal: C12.2, D13.2 (A), Q14.2 (G), R15.2; also elsewhere on the board
/Horn_GPIO_IN: Q14.1 (D), R43.2, TP12.1; also elsewhere on the board
/Ign_OFF_GPIO: Q7.1 (D), R36.2, TP5.1; also elsewhere on the board
/Ign_arr_GPIO: Q8.1 (D), R37.2, TP6.1; also elsewhere on the board
/Ign_arr_Signal: C6.2, D7.2 (A), Q8.2 (G), R6.2; also elsewhere on the board
/Ign_mtr_GPIO: Q9.1 (D), R38.2, TP7.1; also elsewhere on the board
/Ign_mtr_Signal: C7.2, D8.2 (A), Q9.2 (G), R7.2; also elsewhere on the board
/Ign_off_Signal: C5.2, D6.2 (A), Q7.2 (G), R5.2; also elsewhere on the board
/Left_Blinker_ON: Q16.1 (D), R57.2, TP15.1; also elsewhere on the board
/Left_Blinker_Signal: C14.2, D15.2 (A), Q16.2 (G), R17.2; also elsewhere on the board
/Neutral_Gear_GPIO: Q4.1 (D), R34.2, TP3.1; also elsewhere on the board
/Neutral_Gear_Signal: C3.2, D3.2 (A), Q4.2 (G), R3.2; also elsewhere on the board
/PTT_GPIO_IN: Q18.1 (D), R67.2, TP14.1; also elsewhere on the board
/PTT_Signal: C28.2, D17.2 (A), Q18.2 (G), R45.2; also elsewhere on the board
/Regen_Enable_GPIO_IN: Q12.1 (D), R41.2, TP10.1; also elsewhere on the board
/Regen_Enable_Signal: C10.2, D11.2 (A), Q12.2 (G), R13.2; also elsewhere on the board
/Rev_SW_GPIO: Q5.1 (D), R35.2, TP4.1; also elsewhere on the board
/Rev_SW_Signal: C4.2, D5.2 (A), Q5.2 (G), R4.2; also elsewhere on the board
/Right_Blinker_ON: Q15.1 (D), R44.2, TP13.1; also elsewhere on the board
/Right_Blinker_Signal: C13.2, D14.2 (A), Q15.2 (G), R16.2; also elsewhere on the board
GND: C2.1, C3.1, C4.1, C5.1, C6.1, C7.1, C8.1, C9.1, C10.1, C11.1, C12.1, C13.1, C14.1, C28.1, Q3.3 (S), Q4.3 (S), Q5.3 (S), Q7.3 (S), Q8.3 (S), Q9.3 (S), Q10.3 (S), Q11.3 (S), Q12.3 (S), Q13.3 (S), Q14.3 (S), Q15.3 (S), Q16.3 (S), Q18.3 (S), R2.1, R3.1, R4.1, R5.1, R6.1, R7.1, R8.1, R12.1, R13.1, R14.1, R15.1, R16.1, R17.1, R18.2, R19.2, R20.2, R21.2, R22.2, R23.2, R24.2, R25.2, R26.2, R27.2, R28.2, R29.2, R30.2, R45.1, R46.2; also elsewhere on the board
unnamed: D2.1 (K), R18.1
unnamed: D3.1 (K), R19.1
unnamed: D5.1 (K), R20.1
unnamed: D6.1 (K), R21.1
unnamed: D7.1 (K), R22.1
unnamed: D8.1 (K), R23.1
unnamed: D9.1 (K), R24.1
unnamed: D10.1 (K), R25.1
unnamed: D11.1 (K), R26.1
unnamed: D12.1 (K), R27.1
unnamed: D13.1 (K), R28.1
unnamed: D14.1 (K), R29.1
unnamed: D15.1 (K), R30.1
unnamed: D17.1 (K), R46.1

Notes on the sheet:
NMOS 24v -> 3.3v Signal Converter
